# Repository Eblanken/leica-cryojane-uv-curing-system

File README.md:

# leica-cryojane-uv-curing-system

Reverse engineering artifacts and replacement design for Leica's CryoJane UV curing system.

## Layout

| Path | What it holds |
|---|---|
| `hardware/reverse_engineered/` | KiCad captures of existing boards. Each project has its own folder. |
| `hardware/products/` | KiCad projects for the replacement design. |
| `firmware/` | PlatformIO projects for the replacement design. |
| `scripts/` | Bench notebooks, one folder per experiment with `data/` and `results/`. Shared acquisition and mux firmware sit at the top level. |
| `src/cryojane_bench/` | Python shared by the scripts: instrument drivers, log and logger readers, plateau detection, thermistor maths. |
| `tests/` | Tests for `src/`. They need no hardware. |
| `docs/` | Bench procedures and design notes. |

Python belongs in `src/` once a second script needs it. Data lives with the experiment that produced it.

## Setup

Install [pixi](https://pixi.sh), then:

```
pixi install
pixi run test              # Run the tests.
pixi run format            # Apply Black to the Bluesky code.
pixi run list-instruments  # Show attached COM ports.
pixi run lab               # Open the notebooks.
pixi run -e firmware pio --version  # PlatformIO lives in its own environment.
```

## Bench instruments

| Instrument | Package | USB identity |
|---|---|---|
| GW Instek GDM-8341 meter | `src/instruments/gdm8341/` | VID:PID 2184:0030 |
| XL9535 relay mux via ESP32 bridge | `src/instruments/xl9535_relay_mux/` | VID 303A |
| Eastwood QR101B-1M-R1 resistance box | `src/instruments/qr101b/` | VID:PID 1A86:7523 (generic CH340) |

## Experiment data

New acquisition runs through [Bluesky](https://blueskyproject.io/) plans. Each run is one JSON Lines file of event-model documents, written by suitcase-jsonl, holding the data, its units, every instrument's identity and settings, and how the run ended. `cryojane_bench.runs.load_run` reads one back into pandas.

| Experiment | Plan | Runs |
|---|---|---|
| QR101B against GDM-8341 | `scripts/instrument_checks/qr101b_gdm8341_validation/qr101b_gdm8341_validation.py` | `scripts/instrument_checks/qr101b_gdm8341_validation/data/` |
| Passive sensor sweep | `scripts/sensor_characterization/acquisition.py` | `scripts/sensor_characterization/runs/` |
| QR101B output gaps | `scripts/instrument_checks/qr101b_gap_probe/qr101b_gap_probe.py` | `scripts/instrument_checks/qr101b_gap_probe/data/` |
| Series resistor, through the mux | `scripts/duty_cycle_characterization/characterize_series_resistor.py` | `scripts/duty_cycle_characterization/runs/` |
| Duty cycle against sensor resistance, two devices | `scripts/duty_cycle_characterization/duty_vs_sensor_resistance.py` | `scripts/duty_cycle_characterization/runs/` |

The plan scripts take `--simulate` for a dry run without hardware, except the gap probe. The duty-cycle bench's wiring is in `scripts/duty_cycle_characterization/bench.py`. `scripts/instrument_checks/qr101b_gdm8341_validation/qr101b_gdm8341_validation.ipynb` plots the QR101B against the GDM-8341 from a run file.

## Current results

Run the notebooks in this order, because the second reads the first one's `results/fit_summary.csv`:

1. `scripts/sensor_characterization/sensor_characterization.ipynb`: passive Steinhart-Hart and heater resistance fits, referenced to a HOBO logger.
2. `scripts/heater_characterization/heater_characterization.ipynb`: powered behaviour and regulation points, referenced to the chamber probe.

`scripts/sensor_characterization/sensor_characterization_bluesky.ipynb` repeats the first analysis from the sweep's Bluesky run in `runs/`, and checks that it gives the same fits.

`docs/setpoint_bench_test.md` has the planned test to confirm the regulation points.

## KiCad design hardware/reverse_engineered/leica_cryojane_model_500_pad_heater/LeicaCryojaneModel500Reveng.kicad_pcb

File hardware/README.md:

# Hardware

- `reverse_engineered/`: captures of existing boards. Treat these as a record of what the board is, and keep design changes out of them.
- `products/`: KiCad projects for the replacement design.

Each KiCad project gets its own folder. Put libraries used by one project inside its folder. Add a shared `hardware/libraries/` when a second project needs them.

## reverse_engineered/leica_cryojane_model_500_pad_heater

The ECU heater board. The root schematic instantiates `heater.kicad_sch` twice, as the `PAD` and `BATH` sheets.

Sense and drive for each channel:
- The thermistor connects between `HEATER_SENSE` (P1.3 on PAD) and GND (P1.2), with a 10 kohm pull-up to +5 V (R101).
- The heater connects between the +60 V net (P1.1) and `HEATER_LOAD` (P1.4), switched low-side by a CMPTA14 Darlington.
- A 20 kohm trimmer (R106) in a 10 k / 20 k / 10 k divider sets the regulation point, 1.25 V to 3.75 V at the sense comparator.

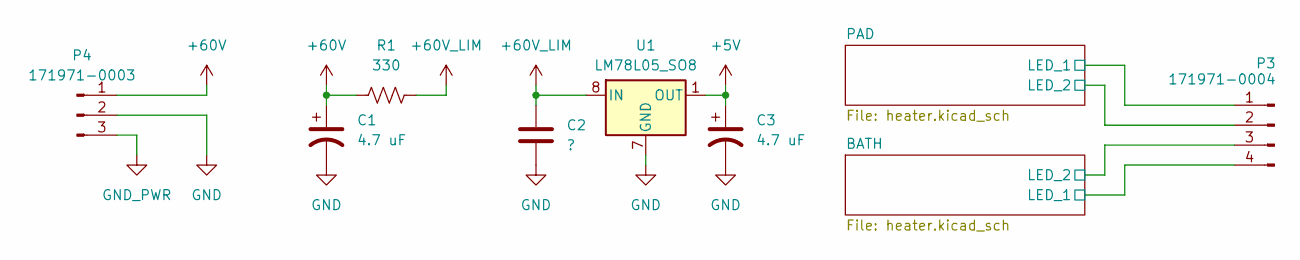
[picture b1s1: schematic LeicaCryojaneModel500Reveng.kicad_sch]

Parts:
C1, C3: 4.7 uF
C2: ?
P3: 171971-0004
P4: 171971-0003
R1: 330
U1: LM78L05_SO8; SOIC-8_3.9x4.9mm_P1.27mm

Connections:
+5V: C3.1, U1.1 (OUT); also elsewhere on the board
+60V: C1.1, P4.1, R1.1; also elsewhere on the board
+60V_LIM: C2.2, R1.2, U1.8 (IN); also elsewhere on the board
/BATH/LED_1: P3.4; also elsewhere on the board
/BATH/LED_2: P3.3; also elsewhere on the board
/PAD/LED_1: P3.1; also elsewhere on the board
/PAD/LED_2: P3.2; also elsewhere on the board
GND: C1.2, C2.1, C3.2, P4.2, U1.2 (GND), U1.3 (GND), U1.6 (GND), U1.7 (GND); also elsewhere on the board
GND_PWR: P4.3; also elsewhere on the board

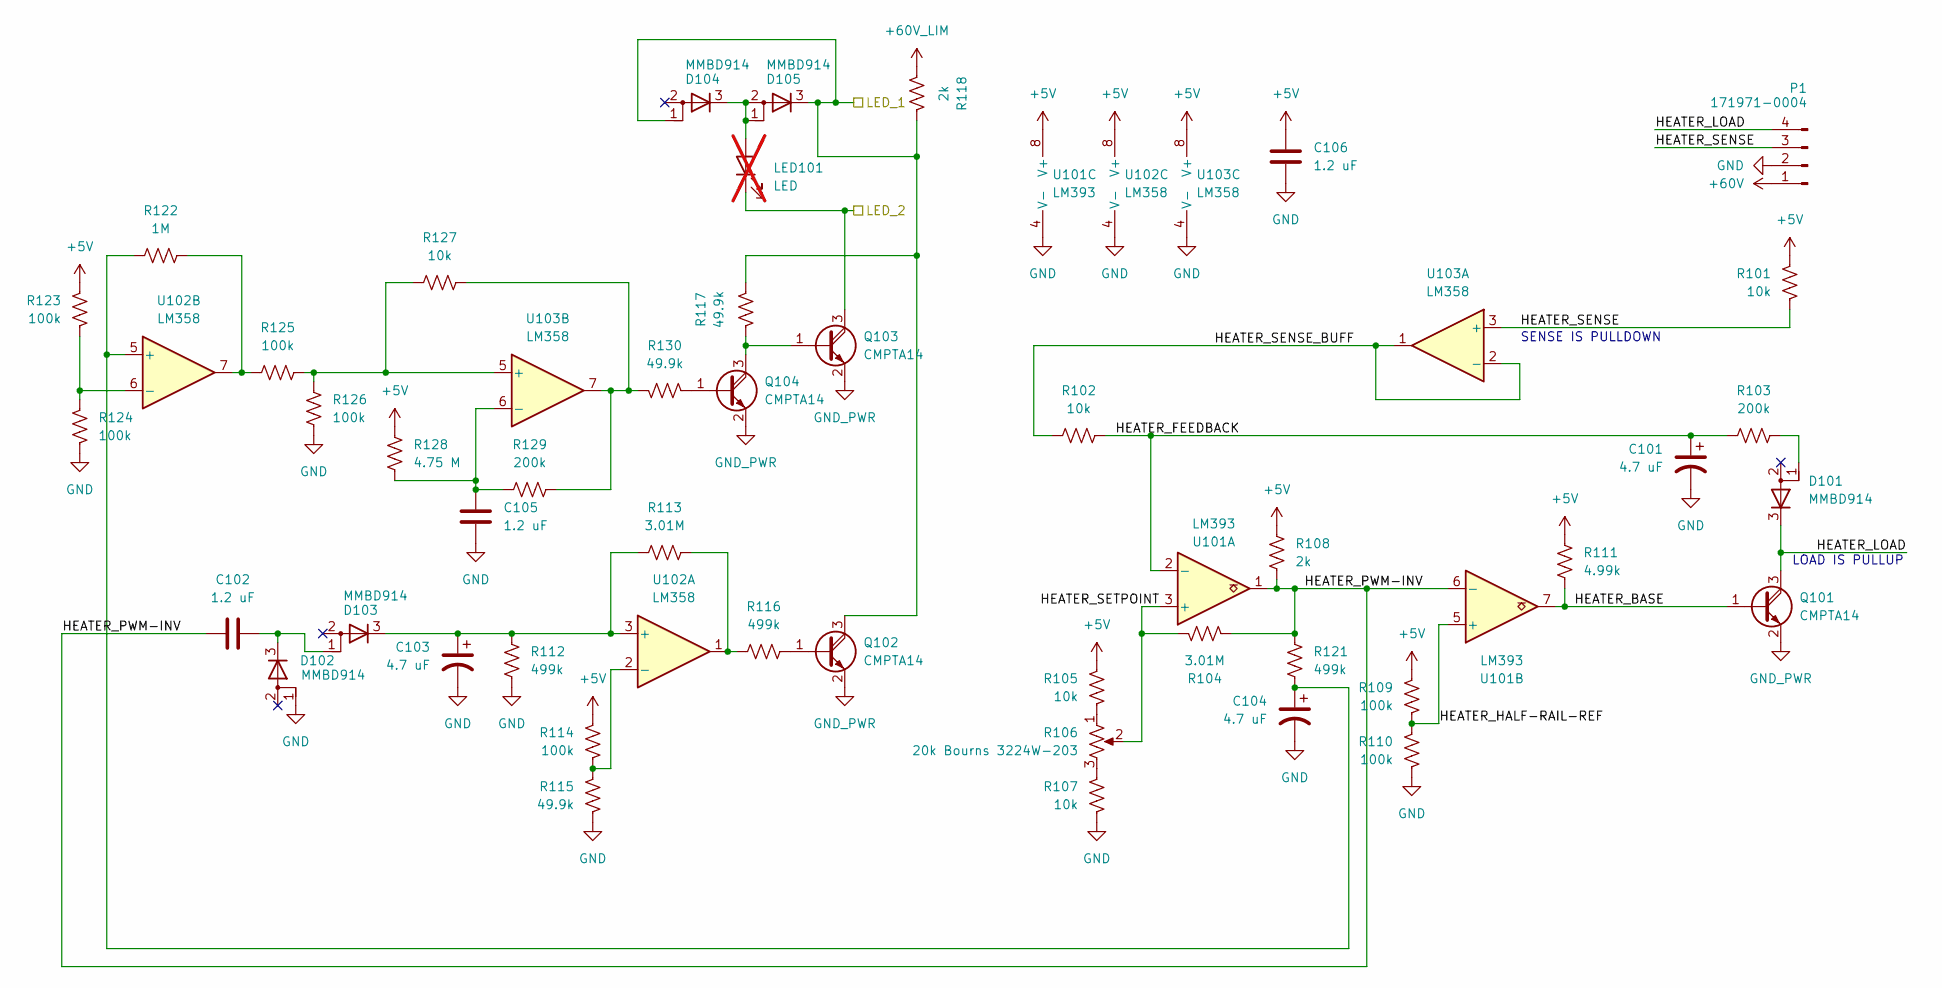
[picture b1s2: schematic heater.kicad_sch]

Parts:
C101, C103, C104: 4.7 uF
C102, C105, C106: 1.2 uF
D101, D102, D103, D104, D105: MMBD914
LED101: LED; not fitted
P1: 171971-0004
Q101, Q102, Q103, Q104: CMPTA14
R101, R102, R105, R107, R127: 10k
R103, R129: 200k
R104, R113: 3.01M
R106: 20k Bourns 3224W-203
R108, R118: 2k
R109, R110, R114, R123, R124, R125, R126: 100k
R111: 4.99k
R112, R116, R121: 499k
R115, R117, R130: 49.9k
R122: 1M
R128: 4.75 M
U101: LM393
U102, U103: LM358

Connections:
+5V: C106.1, R101.2, R105.1, R108.1, R109.1, R111.2, R114.2, R123.1, R128.2, U101.8 (V+), U102.8 (V+), U103.8 (V+); also elsewhere on the board
+60V: P1.1; also elsewhere on the board
+60V_LIM: R118.2; also elsewhere on the board
/PAD/HEATER_BASE: Q101.1 (B), R111.1, U101.7
/PAD/HEATER_FEEDBACK: C101.1, R102.1, R103.2, U101.2 (-)
/PAD/HEATER_HALF-RAIL-REF: R109.2, R110.1, U101.5 (+)
/PAD/HEATER_LOAD: D101.3 (K), P1.4, Q101.3 (C)
/PAD/HEATER_PWM-INV: C102.1, R104.2, R108.2, R121.2, U101.1, U101.6 (-)
/PAD/HEATER_SENSE: P1.3, R101.1, U103.3 (+)
/PAD/HEATER_SENSE_BUFF: R102.2, U103.1, U103.2 (-)
/PAD/HEATER_SETPOINT: R104.1, R106.2, U101.3 (+)
/PAD/LED_1: D104.1 (A), D105.3 (K), Q102.3 (C), R117.1, R118.1; also elsewhere on the board
/PAD/LED_2: LED101.1 (K), Q103.3 (C); also elsewhere on the board
GND: C101.2, C103.2, C104.2, C105.2, C106.2, D102.1 (A), P1.2, R107.2, R110.2, R112.1, R115.1, R124.2, R126.1, U101.4 (V-), U102.4 (V-), U103.4 (V-); also elsewhere on the board
GND_PWR: Q101.2 (E), Q102.2 (E), Q103.2 (E), Q104.2 (E); also elsewhere on the board
unnamed: D101.1 (A), R103.1
unnamed: C102.2, D102.3 (K), D103.1 (A)
unnamed: C103.1, D103.3 (K), R112.2, R113.1, U102.3 (+)
unnamed: D104.3 (K), D105.1 (A), D105.2 (A), LED101.2 (A)
unnamed: Q102.1 (B), R116.1
unnamed: Q103.1 (B), Q104.3 (C), R117.2
unnamed: Q104.1 (B), R130.1
unnamed: R105.2, R106.1
unnamed: R106.3, R107.1
unnamed: R113.2, R116.2, U102.1
unnamed: R122.1, R125.1, U102.7
unnamed: R127.2, R129.2, R130.2, U103.7
unnamed: R114.1, R115.2, U102.2 (-)
unnamed: C104.1, R121.1, R122.2, U102.5 (+)
unnamed: R123.2, R124.1, U102.6 (-)
unnamed: R125.2, R126.2, R127.1, U103.5 (+)
unnamed: C105.1, R128.1, R129.1, U103.6 (-)

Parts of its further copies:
C201, C203, C204: 4.7 uF
C202, C205, C206: 1.2 uF
D201, D202, D203, D204, D205: MMBD914
LED201: LED; not fitted
P2: 171971-0004
Q201, Q202, Q203, Q204: CMPTA14
R201, R202, R205, R207, R227: 10k
R203, R229: 200k
R204, R213: 3.01M
R206: 20k Bourns 3224W-203
R208, R218: 2k
R209, R210, R214, R223, R224, R225, R226: 100k
R211: 4.99k
R212, R216, R221: 499k
R215, R217, R230: 49.9k
R222: 1M
R228: 4.75 M
U201: LM393
U202, U203: LM358

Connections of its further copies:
+5V: C206.1, R201.2, R205.1, R208.1, R209.1, R211.2, R214.2, R223.1, R228.2, U201.8 (V+), U202.8 (V+), U203.8 (V+); also elsewhere on the board
+60V: P2.1; also elsewhere on the board
+60V_LIM: R218.2; also elsewhere on the board
/BATH/HEATER_BASE: Q201.1 (B), R211.1, U201.7
/BATH/HEATER_FEEDBACK: C201.1, R202.1, R203.2, U201.2 (-)
/BATH/HEATER_HALF-RAIL-REF: R209.2, R210.1, U201.5 (+)
/BATH/HEATER_LOAD: D201.3 (K), P2.4, Q201.3 (C)
/BATH/HEATER_PWM-INV: C202.1, R204.2, R208.2, R221.2, U201.1, U201.6 (-)
/BATH/HEATER_SENSE: P2.3, R201.1, U203.3 (+)
/BATH/HEATER_SENSE_BUFF: R202.2, U203.1, U203.2 (-)
/BATH/HEATER_SETPOINT: R204.1, R206.2, U201.3 (+)
/BATH/LED_1: D204.1 (A), D205.3 (K), Q202.3 (C), R217.1, R218.1; also elsewhere on the board
/BATH/LED_2: LED201.1 (K), Q203.3 (C); also elsewhere on the board
GND: C201.2, C203.2, C204.2, C205.2, C206.2, D202.1 (A), P2.2, R207.2, R210.2, R212.1, R215.1, R224.2, R226.1, U201.4 (V-), U202.4 (V-), U203.4 (V-); also elsewhere on the board
GND_PWR: Q201.2 (E), Q202.2 (E), Q203.2 (E), Q204.2 (E); also elsewhere on the board
unnamed: D201.1 (A), R203.1
unnamed: C202.2, D202.3 (K), D203.1 (A)
unnamed: C203.1, D203.3 (K), R212.2, R213.1, U202.3 (+)
unnamed: D204.3 (K), D205.1 (A), D205.2 (A), LED201.2 (A)
unnamed: Q202.1 (B), R216.1
unnamed: Q203.1 (B), Q204.3 (C), R217.2
unnamed: Q204.1 (B), R230.1
unnamed: R205.2, R206.1
unnamed: R206.3, R207.1
unnamed: R213.2, R216.2, U202.1
unnamed: R222.1, R225.1, U202.7
unnamed: R227.2, R229.2, R230.2, U203.7
unnamed: R214.1, R215.2, U202.2 (-)
unnamed: C204.1, R221.1, R222.2, U202.5 (+)
unnamed: R223.2, R224.1, U202.6 (-)
unnamed: R225.2, R226.2, R227.1, U203.5 (+)
unnamed: C205.1, R228.1, R229.1, U203.6 (-)

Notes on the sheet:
LOAD IS PULLUP
SENSE IS PULLDOWN

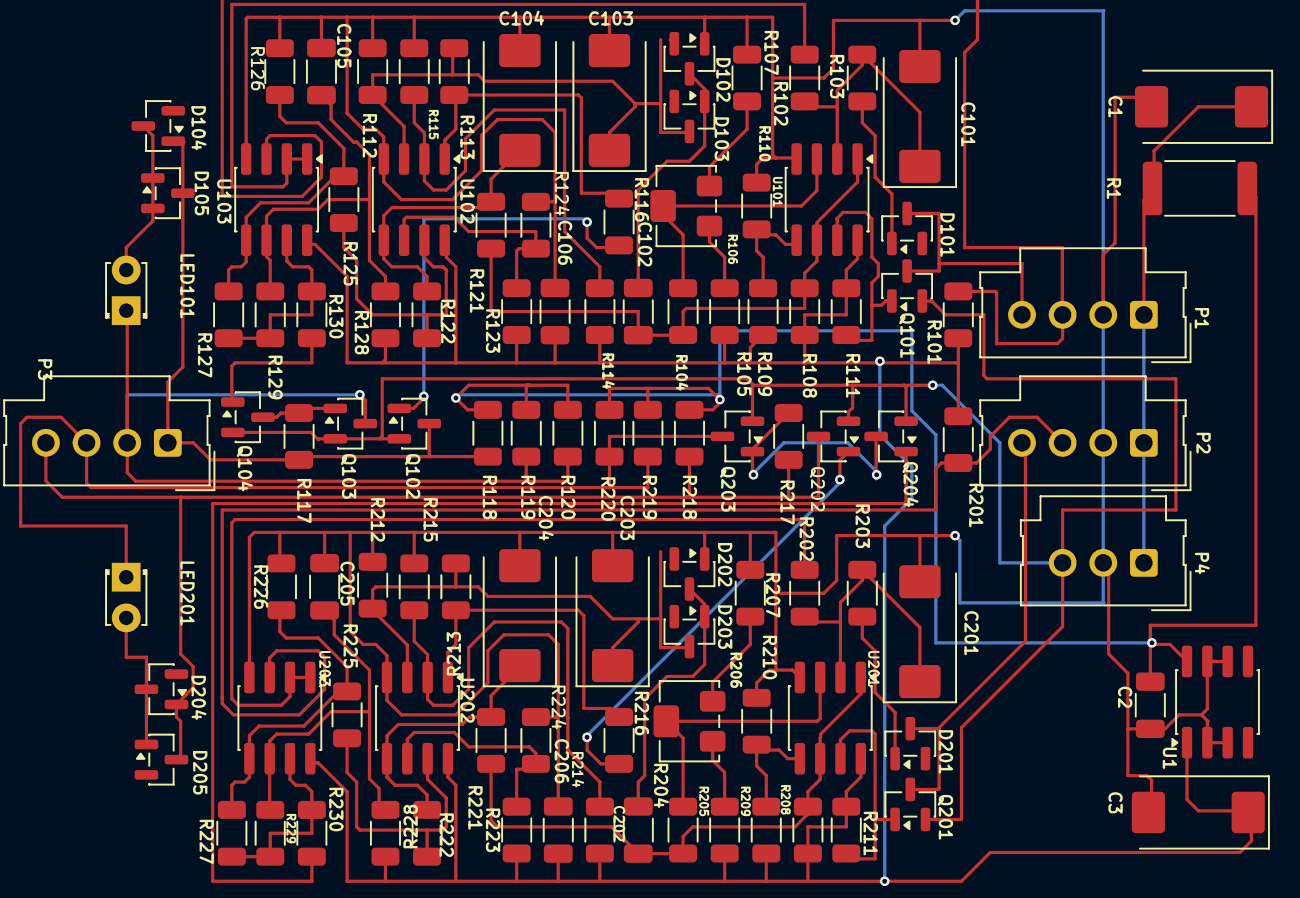
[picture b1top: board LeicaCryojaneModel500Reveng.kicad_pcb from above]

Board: 2 copper layers, 107 parts (0 on the bottom side), 59 nets.

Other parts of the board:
R119, R120, R219, R220: R_1206_3216Metric

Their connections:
+60V_LIM: R119.2, R120.2, R219.2, R220.2; also elsewhere on the board
/BATH/LED_2: R219.1, R220.1; also elsewhere on the board
/PAD/LED_2: R119.1, R120.1; also elsewhere on the board
